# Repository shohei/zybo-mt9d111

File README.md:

# MT9D111-ZYBO inteface circuit

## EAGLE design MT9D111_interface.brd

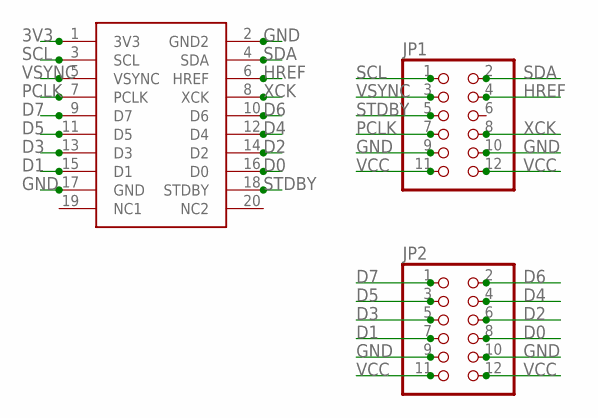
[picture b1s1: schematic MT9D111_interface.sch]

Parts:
JP1, JP2: PINHD-2X6; 2X06
U$1: MT9D111; 10-2

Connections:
3V3: U$1.1 (3V3)
D0: JP2.8, U$1.16 (D0)
D1: JP2.7, U$1.15 (D1)
D2: JP2.6, U$1.14 (D2)
D3: JP2.5, U$1.13 (D3)
D4: JP2.4, U$1.12 (D4)
D5: JP2.3, U$1.11 (D5)
D6: JP2.2, U$1.10 (D6)
D7: JP2.1, U$1.9 (D7)
GND: JP1.9, JP1.10, JP2.9, JP2.10, U$1.2 (GND2), U$1.17 (GND)
HREF: JP1.4, U$1.6 (HREF)
PCLK: JP1.7, U$1.7 (PCLK)
SCL: JP1.1, U$1.3 (SCL)
SDA: JP1.2, U$1.4 (SDA)
STDBY: JP1.5, U$1.18 (STDBY)
VCC: JP1.11, JP1.12, JP2.11, JP2.12
VSYNC: JP1.3, U$1.5 (VSYNC)
XCK: JP1.8, U$1.8 (XCK)

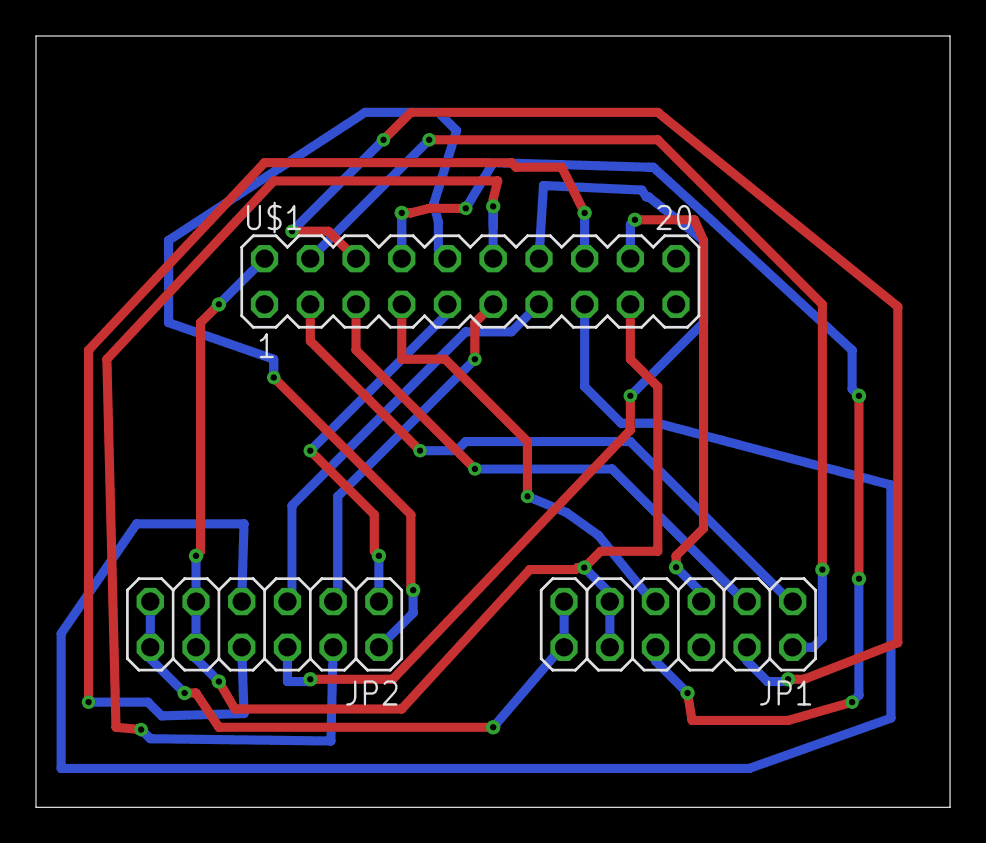
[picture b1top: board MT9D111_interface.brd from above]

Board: 2 copper layers, 50.8 x 42.9 mm, 3 parts (0 on the bottom side), 17 nets.

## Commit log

2017-05-15 add mill 'n drill data
2017-05-15 add image
